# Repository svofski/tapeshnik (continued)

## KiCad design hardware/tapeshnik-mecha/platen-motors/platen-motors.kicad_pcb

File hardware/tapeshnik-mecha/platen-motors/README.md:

# TAPESHNIK Platen-Motors

This is platen #1 of TAPESHNIK-MECHA. It has the motors and the motor control board mounted behind them.

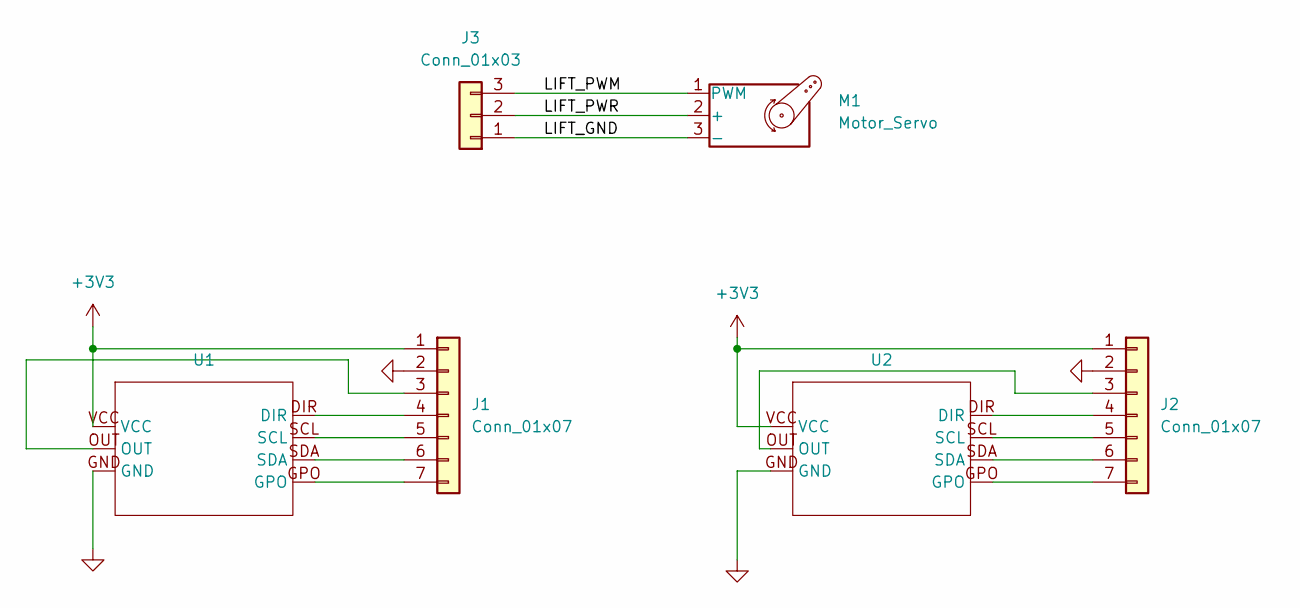
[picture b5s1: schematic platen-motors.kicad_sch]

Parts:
J1, J2: Conn_01x07; PinHeader_1x07_P2.54mm_Vertical
J3: Conn_01x03; PinHeader_1x03_P2.54mm_Vertical
M1: Motor_Servo; PinHeader_1x03_P2.54mm_Vertical
U1, U2: AS5600-breakout-23x23

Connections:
+3V3: J1.1, J2.1, U1.VCC, U2.VCC
/LIFT_GND: J3.1, M1.3 (-)
/LIFT_PWM: J3.3, M1.1 (PWM)
/LIFT_PWR: J3.2, M1.2 (+)
GND: J1.2, J2.2, U1.GND, U2.GND
unnamed: J1.3, U1.OUT
unnamed: J1.4, U1.DIR
unnamed: J1.5, U1.SCL
unnamed: J1.6, U1.SDA
unnamed: J1.7, U1.GPO
unnamed: J2.3, U2.OUT
unnamed: J2.4, U2.DIR
unnamed: J2.5, U2.SCL
unnamed: J2.6, U2.SDA
unnamed: J2.7, U2.GPO

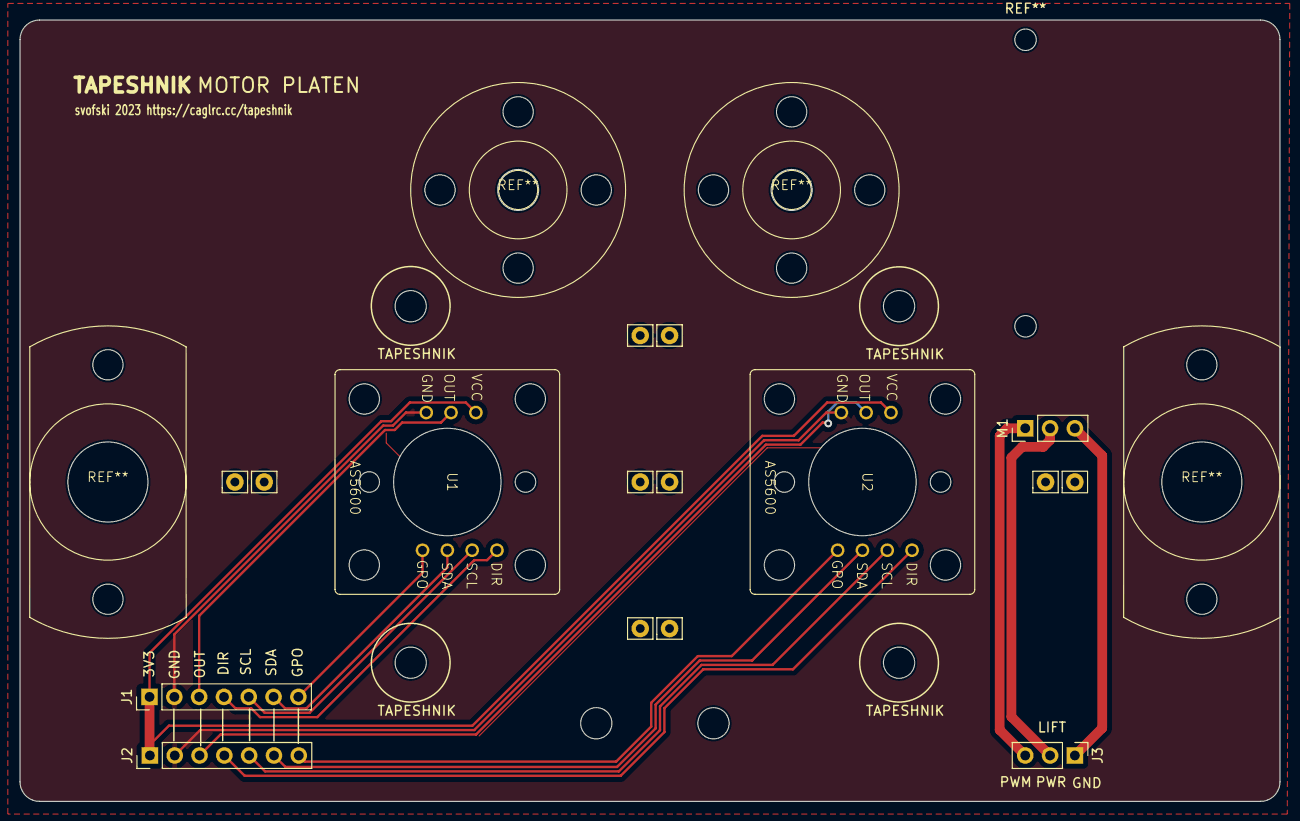
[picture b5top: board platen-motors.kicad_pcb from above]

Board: 2 copper layers, 129.0 x 80.0 mm, 6 parts (0 on the bottom side), 15 nets.

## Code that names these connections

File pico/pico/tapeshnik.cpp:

/**
 * Copyright (c) 2023 svofski
 */

#include <stdio.h>
#include "pico/stdlib.h"
#include "hardware/gpio.h"
#include "hardware/pwm.h"

#include "config.h"

#include "debounce.h"
#include "wheel.h"
#include "mainloop.h"
#include "tacho.h"
#include "bitstream.h"
#include "util.h"

#define ML_NO_REQUEST   0
#define ML_STOP_REQUEST ' '
volatile int mainloop_request = ML_NO_REQUEST;

Boost boost(GPIO_EBOOST);
Motor motor(boost, GPIO_MOTOR_CONTROL);
Solenoid solenoid(GPIO_SOLENOID_CONTROL);
Wheel wheel(motor, solenoid, GPIO_MODE_ENTRY);
Bitstream bstream(wheel, GPIO_RDHEAD, GPIO_WRHEAD, GPIO_WREN, GPIO_READ_LED,
        GPIO_WRITE_LED);

void request_wheel_stop()
{
    mainloop_request = ML_STOP_REQUEST;
}

char tacho_counter_str[16];
int last_tacho_counter = -1;
int last_wheel_position = -1;
int last_motor_status = -1;

int slice_num;

void freq_sweep()
{
    gpio_set_function(GPIO_WRHEAD, GPIO_FUNC_PWM);
    slice_num = pwm_gpio_to_slice_num(GPIO_WRHEAD);   // GP16, pin 21
    pwm_set_clkdiv_int_frac(slice_num, 62, 8);   // pwm slice frequency 125MHz/62.5 = 2MHz
    // useful sweep range: 100Hz..20000Hz
    // wrap = [2e6/100..2e6/20000] = [20000..100]
    pwm_set_enabled(slice_num, true);
    
    printf("linear sweep %d..%d Hz... on pin 21 ", 2000000/20000, 2000000/100);
    for (int i = 20000; i >= 100; --i) {
        pwm_set_wrap(slice_num, i);
        pwm_set_chan_level(slice_num, PWM_CHAN_A, i >> 1);
        sleep_ms(2);
    }
    pwm_set_enabled(slice_num, false);
    printf("done\n");
}

void freq_8(int hz)
{
    gpio_set_function(GPIO_WRHEAD, GPIO_FUNC_PWM);
    auto slice_num = pwm_gpio_to_slice_num(GPIO_WRHEAD);   // GP16, pin 21
    pwm_set_clkdiv_int_frac(slice_num, 62, 8);   // pwm slice frequency 125MHz/62.5 = 2MHz
    // useful sweep range: 100Hz..20000Hz
    // wrap = [2e6/100..2e6/20000] = [20000..100]
    pwm_set_enabled(slice_num, true);
    
    printf("20sec of %d Hz... on pin 21 ", hz);
    int div = static_cast<int>(125000000/62.5/hz);
    pwm_set_wrap(slice_num, div);
    pwm_set_chan_level(slice_num, PWM_CHAN_A, div >> 1);
    //sleep_ms(20000);
    //pwm_set_enabled(slice_num, false);
    //gpio_set_function(GPIO_WRHEAD, GPIO_FUNC_NULL);
    //printf("done\n");
}

void freq_stop()
{
    pwm_set_enabled(slice_num, false);
    gpio_set_function(GPIO_WRHEAD, GPIO_FUNC_NULL);
}

int main() {
    stdio_init_all();

    printf("tapeshnik\n");

    debounce_init();
    //wheel_init(GPIO_MOTOR_CONTROL, GPIO_SOLENOID_CONTROL, GPIO_MODE_ENTRY);

    tacho_init(GPIO_TACHO);

    wheel.init();

    //gpio_disable_pulls(GPIO_RDHEAD);
    //gpio_pull_up(GPIO_RDHEAD);
    //gpio_set_dir(GPIO_RDHEAD, /* out */ true);
    //gpio_put(GPIO_RDHEAD, 1);

    // Wait forever
    while (1) {
        int c = mainloop_request;
        mainloop_request = ML_NO_REQUEST;
        if (c == ML_NO_REQUEST) {
            c = getchar_timeout_us(100);
            if (mainloop_request != ML_NO_REQUEST) {
                c = mainloop_request;
            }
        }
        switch (c) {
            case 'z': solenoid.pulse_ms(50);
                      break;
            case 'm': motor.enable(!motor.get_status());
                      printf("motor=%d\n", motor.get_status());
                      break;
            case ' ': wheel.stop();
                      freq_stop();
                      break;
            case 'p': wheel.play();
                      break;
            case 'f': wheel.ff();
                      break;
            case 'r': wheel.rew();
                      break;
            case '0': tacho_set_counter(0);
                      break;
            case 's': freq_sweep();
                      break;
            case '4': freq_8(4000);
                      break;
            case '8': freq_8(8000);
                      break;
            case '1': freq_8(10000);
                      break;
            case '2': freq_8(20000);
                      break;
            case '3': freq_8(30000);
                      break;
            //case '5': bstream.test();
            //          break;
            //case 'w': bstream.test(BS_TX);
            //          break;
            //case 'l': bstream.test(BS_RX);
            //          break;
            //case 'e': bstream.test_sector_rewrite();
            //          break;
            case 'F': bstream.llformat();
                      break;
            case 'l': bstream.sector_scan(65535);
                      break;
            case 'w': bstream.test_write();
                      break;
            case 10:
            case 13:
                      info_println("\nHelp: m=motor, p=play, f=ff, r=rew, space=stop, 0=zero counter");
                      break;
        }

        if (tacho_get_counter() != last_tacho_counter
                || wheel.get_position() != last_wheel_position
                || motor.get_status() != last_motor_status) {
            last_tacho_counter = tacho_get_counter();
            last_wheel_position = wheel.get_position();
            last_motor_status = motor.get_status();
            snprintf(tacho_counter_str, 16, "  %+05d    \r", last_tacho_counter);
            
            int bgcolor = last_motor_status ? 44 : 42;
            switch (last_wheel_position) {
                case WP_STOP:
                    blink_off();
                    print_color(bgcolor, 37, "   STOP  ", tacho_counter_str);
                    break;
                case WP_PLAY:
                    blink_on();
                    print_color(bgcolor, 37, " <|PLAY  ", tacho_counter_str);
                    break;
                case WP_FF:
                    blink_on();
                    print_color(bgcolor, 37, "  <<FF   ", tacho_counter_str);
                    break;
                case WP_REW:
                    blink_on();
                    print_color(bgcolor, 37, "  REW>>  ", tacho_counter_str);
                    break;
            }
        }
    };

    return 0;
}

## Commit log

2023-07-02 lala
2023-07-02 sources
2023-07-02 detect too fast spin in play mode
2023-07-10 log update
2023-07-22 updated the head amplifiers circuit
2023-07-22 stepping up to c++
2023-07-22 added bitstream
2023-07-22 kicad files
2023-08-02 libcorrect f5a28c74fba7a99736fe49d3a5243eca29517ae9
    correct.h updated for c++ compatibility
2023-08-02 modbus crc16
    by Tiago Ventura
    taken from https://github.com/LacobusVentura/MODBUS-CRC16/
2023-08-02 moving thing around, renaming to make more sense
2023-08-03 wip.. some stuff works
2023-08-04 just wip
2023-08-05 mfm send-receive on a loopback wire
    wire between gpio 16 and 17
    super-naiive rx tolerates slightly faster send, but not slower
2023-08-05 dll tracking of mfm with pid, etc
    more artificial tests before i'm ready for running it on tape. dll
    tracker shows slightly better performance than fixed, but it's not a
    miracle yet. i think real tuning it up will only make sense with real
    tape tests.
2023-08-05 add fec to the test, sector data, recovery
2023-08-11 downshifted to fm and 3300 hz
    seems to work ~275cps net
    naiive loop works in offline tests but seems to be less robust on
    hardware. delay-locked loop is still the most robust.
2023-08-12 refactoring test mess into something usable
2023-08-14 tape sector overwrite experiment in progress
    pipico ded, working on the new pcb instead
2023-08-20 schematic updated and boards sent for fab
2023-08-20 sx1308
2023-08-20 pcb layout
2023-08-20 12v paranoid
2023-08-21 motor
2023-09-01 kicad files for the mecha and motor controller
2023-09-03 adding a lot of mecha-specific stuff
2023-09-03 + ecma standard
2023-09-03 cassette dimensions screenshot
2023-10-01 updated schematics
2023-10-01 power sequencer switch circuit picture
2023-10-01 photo of proto2 bodges
2023-10-02 colourful printing of sector info
2023-10-02 succesfully replaced a sector
2023-10-02 encoding was weirded, hopefully fixed
    stuff seems more steady now, need more verification
    current speed seems too fast, there are errors. but it's cool
2023-10-03 fine working stuff before complete teardown
    new version will have fixed sectors
2023-10-05 hardsectors wip
2023-10-06 hard sector numbers can be read back
2023-10-06 sectors read, but annoying crc16 in every chunk
2023-10-06 sector rewrite works
2023-10-11 kicad file updates
2023-10-11 updated 12v circuit
2023-10-12 reading retries continued
    some scan loop optimisations, some retry fixes
    next: data interleave and random seeks
2025-12-08 updates kicad files + doc
2025-12-08 pictures
2025-12-08 photo
2025-12-28 HelloFOC, as is
    will need a cleanup or a rewrite even
2025-12-31 Enhance index with Iteration 1 and 2 details
    Expanded the index with details on Iteration 1 and Iteration 2 experiments, including descriptions and links to related resources.
2026-01-01 Update index.md
    feck off copilot
2026-02-04 generate compile_commands.json
2026-02-04 hellofoc update
2026-02-04 update-compiledb.sh
